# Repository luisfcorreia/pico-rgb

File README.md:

# pico-rgb
a pcb for an image generator for testing old monitors

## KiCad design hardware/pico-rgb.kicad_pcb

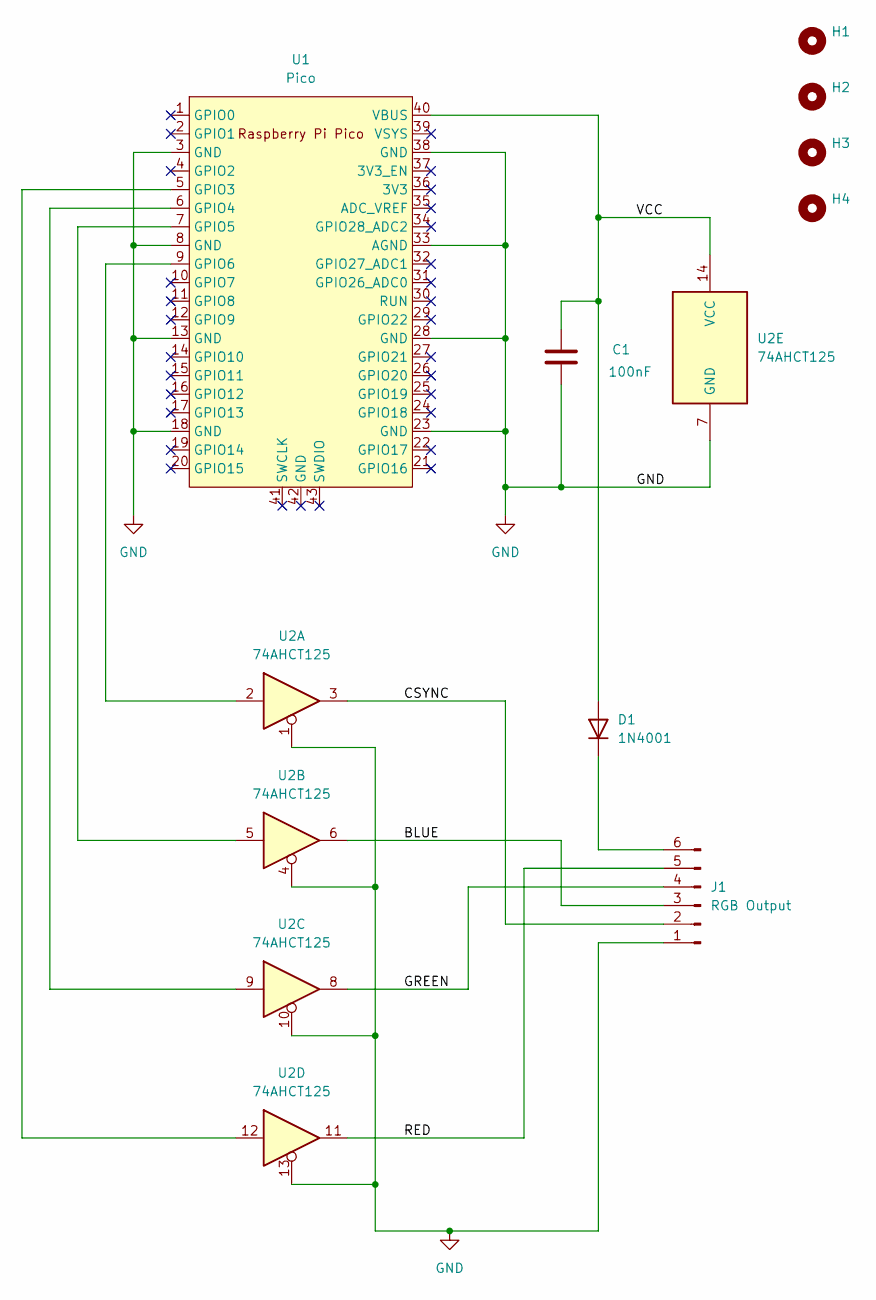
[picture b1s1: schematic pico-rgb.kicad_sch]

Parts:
C1: 100nF; C_Disc_D5.0mm_W2.5mm_P2.50mm
D1: 1N4001; D_DO-41_SOD81_P10.16mm_Horizontal
H1, H2, H3, H4: MountingHole; MountingHole_2.2mm_M2
J1: RGB Output; PinHeader_1x06_P2.54mm_Vertical
U1: Pico; RPi_Pico_SMD_TH
U2: 74AHCT125; DIP-14_W7.62mm_LongPads

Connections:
/BLUE: J1.3, U2.6
/CSYNC: J1.2, U2.3
/GREEN: J1.4, U2.8
/RED: J1.5, U2.11
/VCC: C1.1, D1.2 (A), U1.40 (VBUS), U2.14 (VCC)
GND: C1.2, J1.1, U1.3 (GND), U1.8 (GND), U1.13 (GND), U1.18 (GND), U1.23 (GND), U1.28 (GND), U1.33 (AGND), U1.38 (GND), U2.1, U2.4, U2.7 (GND), U2.10, U2.13
unnamed: D1.1 (K), J1.6
unnamed: U1.5 (GPIO3), U2.12
unnamed: U1.6 (GPIO4), U2.9
unnamed: U1.7 (GPIO5), U2.5
unnamed: U1.9 (GPIO6), U2.2

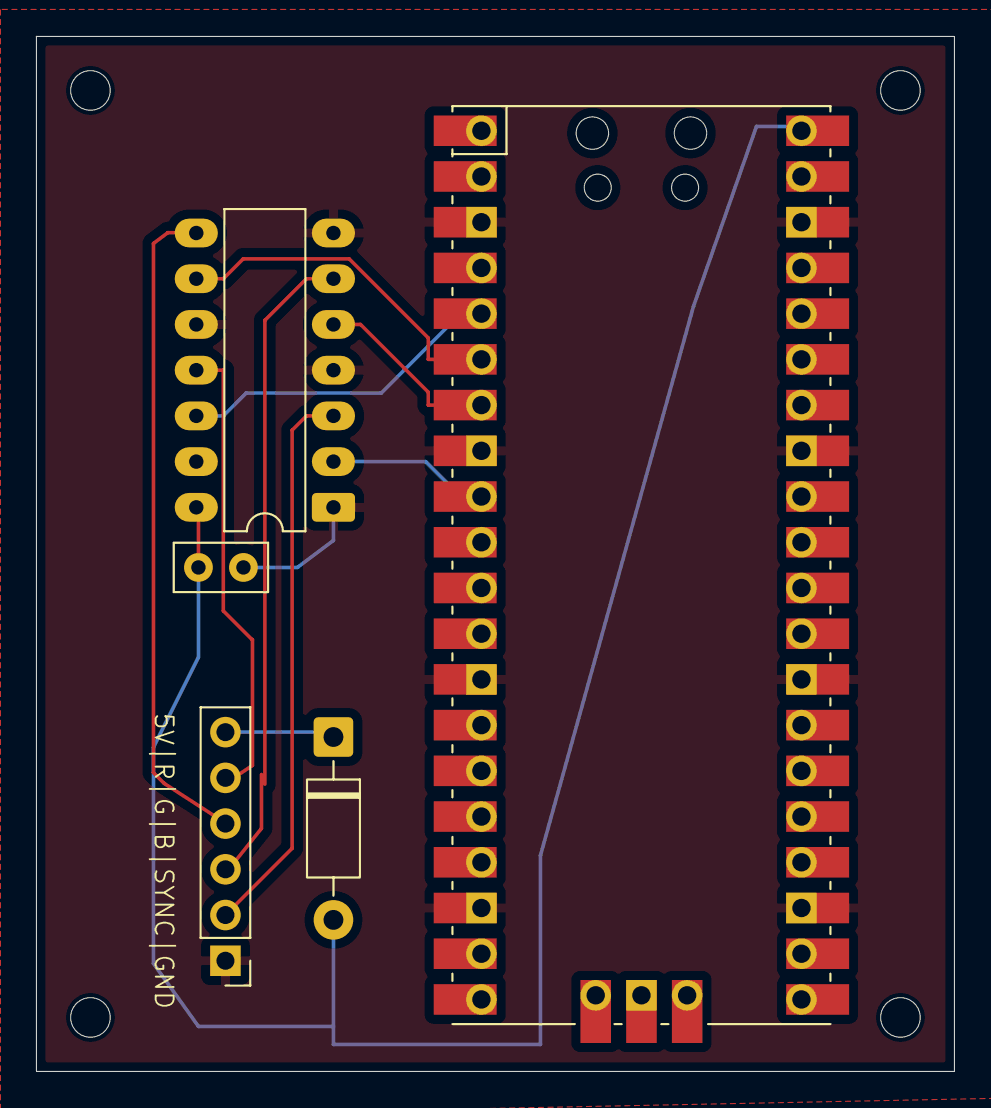
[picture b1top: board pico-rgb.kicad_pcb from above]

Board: 2 copper layers, 51.0 x 57.5 mm, 9 parts (0 on the bottom side), 11 nets.

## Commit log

2025-09-03 initial crimes
2025-09-04 shuffle stuff around and add software, still WiP
